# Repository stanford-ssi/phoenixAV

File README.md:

# phoenixAV

This is the avionics repository for Project Phoenix, a staged rocket for the FAR 1030 competition. 

Kicad footprints, pcb files for Passion Fruit Orange Guava, and flight code (Teensy 3.6)

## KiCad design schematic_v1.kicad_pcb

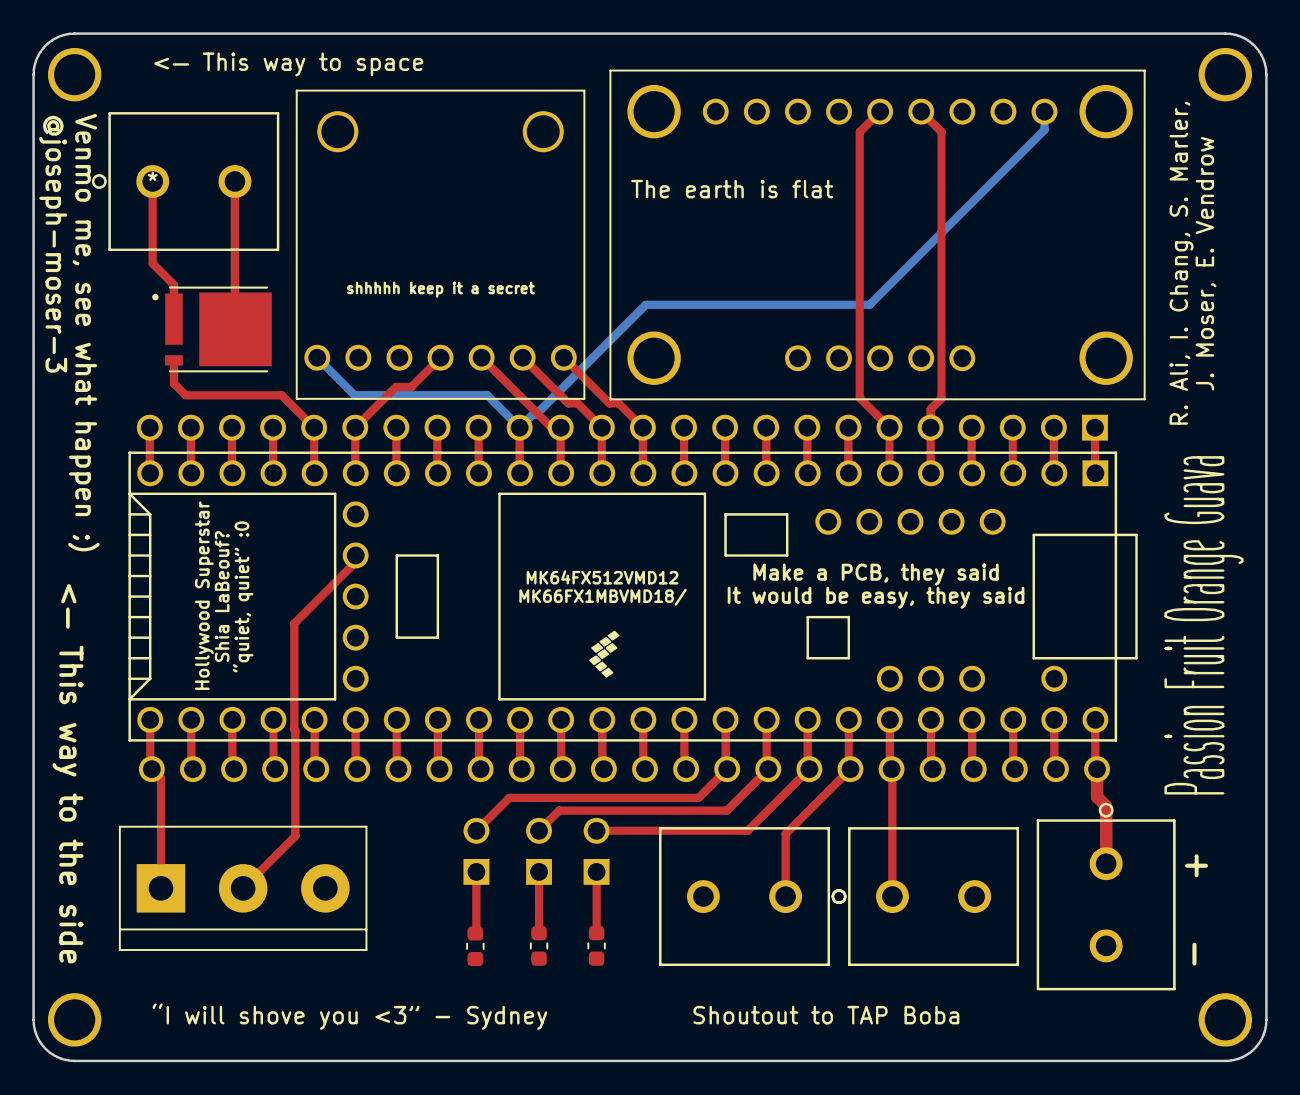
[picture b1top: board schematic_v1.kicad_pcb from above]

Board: 2 copper layers, 76.2 x 63.5 mm, 15 parts (0 on the bottom side), 22 nets.

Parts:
D1, D2, D3: LED; led
J2, J3, J4, J6: Conn_01x02_Female; Terminal_block
J5: Conn_01x03_Female; TerminalBlock_bornier-3_P5.08mm
Q1: BSC012N06NSATMA1; TRANS_BSC012N06NSATMA1
R1, R2, R3: 1K; R_0603_1608Metric
U1: Teensy3.6; Teensy35_36
U2: LSM9DS1; DOF9_Gyro_LSM9DS1
U3: BMP280

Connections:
+5V: J4.1, U1.53
/BMP_CS: U1.12, U3.7
/BMP_SCK: U1.19, U3.4
/BMP_SDI: U1.13, U3.6
/BMP_SDO: U1.14, U3.5
/BSC_pin1: J6.1, Q1.1
/BSC_pin2: J6.2, Q1.8
/CONN_J2: J2.1, U1.47
/CONN_J3: J3.1, U1.48
/DOF_SCL: U1.5, U2.4
/DOF_SDA: U1.6, U2.5
/GEN_VIN: U1.15, U2.1, U3.1
/HALL_SIG: J5.1, U1.30
/HALL_VIN: J5.2, U1.26
/LED1: D1.2, U1.46
/LED2: D2.2, U1.45
/LED3: D3.2, U1.44
/bsc_sig: Q1.4, U1.20
GND: J2.2, J3.2, J4.2, J5.3, R1.2, R2.2, R3.2, U1.1, U2.3, U3.3
unnamed: D1.1, R1.1
unnamed: D2.1, R2.1
unnamed: D3.1, R3.1

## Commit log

2019-11-04 Initialized ReadMe
2020-02-19 Add files via upload
    Footprints for all large sensors
2020-02-28 Added arduino code
2020-04-02 PCB files for Passionfruit Orange Guava
2020-04-02 Footprints for DOF9, LED, Terminal Block, Teensy3.6

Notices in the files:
parts and their libraries:
Copyright 2016 Accelerated Designs. All rights reserved.
